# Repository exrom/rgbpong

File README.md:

# RGB modification for AY-3-8500 based game consoles

## Problems without an rgb output

The [AY-3-8500](https://en.wikipedia.org/wiki/AY-3-8500) is an integrated circuit from the 1970's used in pong-like video gaming consoles.
These consoles have an antenna output where the video signal is modulated onto a VHF channel.
The video quality is very poor because of the nature of a composite video and the VHF back and forth conversion.

Some consoles have a colored output where the playing field, the ball and the left and right paddle have different colors. This is possible because the AY-3-8500 provides separate signals for them.
A curcuit of logic gates generates different phased color carriers and combies each picture signal with one of them in order to get the colored output.
The color generation is very simple and the resulting composite video signal might not be completely compatible with the standards.
A wrong adjusted color carrier frequency might also lead to a TV not showing the colors at all and fall back to a b/w video.
 
Now there are modifications for having a composite video output for such consoles like 
[this one](https://circuit-board.de/forum/index.php/Thread/11658-Umbau-von-Universum-4106-Color-Video-Out/). 
Though this already provides better video quality as the HF conversion is skipped, the quality and stability of the video is still not perfect.

Composite video signals have - in contrast to rgb - a systematic problem: luminance and color signals disturb each other. Aka [dot crawl](https://en.wikipedia.org/wiki/Dot_crawl).

In my case, i got a UNIVERSUM Multi Color Spiel 4106 with PAL color output and wanted to connect it to a modern flat screen TV which did not show the colors correctly. You might also use this rgb mod to add colored output if your console is just black/white.

## The RGB modification

### AY-3 signals

The AY-3-8500 has this pinout:

.
 
It works with 6...7V. In my case a voltage regulator will limit battery voltage to 6.1V.

We need to connect to these pins:

| signal                         |  pin  |
|--------------------------------|-------|
| Vss (ground)                   |  2    |
| Sound output                   |  3    |
| Vcc (6.1V)                     |  4    |
| Ball output                    |  6    |
| Right player output            |  9    |
| Left player output             |  10   |
| Sync output                    |  16   |
| Score and Field output         |  24   |

All signals are active high (high voltage == bright).

### Color mapping

I decided to map the four signals to the red, green, blue inputs like this:

|          |   ball   | score & field  |  left    |  right   |
|----------|----------|----------------|----------|----------|
| 🔴 red      |    x     |      x         |    x     |          |
| 🟢 green    |    x     |      x         |          |    x     |
| 🔵 blue     |    x     |                |    x     |    x     |
|----------|----------|----------------|----------|----------|
| color    | ⚪ white   |    🟡 yellow     | 🟣 purple  | 😱 sky blue |

(there is no unicode char for sky blue - sorry)

### SCART signals

I decided to interface to a [SCART connector](https://en.wikipedia.org/wiki/SCART) which provides rgb input on a TV - at least in europe.

| signal                         |  pin  |  remark                       |
|--------------------------------|-------|-------------------------------|
| red video                      |  15   |  0.7 Vpp, 75 ohms             |
| green video                    |  11   |  0.7 Vpp, 75 ohms             |
| blue  video                    |  7    |  0.7 Vpp, 75 ohms             |
| RGB video selection            |  16   |  0..0.4V=composite, 1..3V=RGB |
| composite video                |  20   |  1 Vpp, 75 ohms               |
| audio input                    |  2+6  |  0.40 mVrms, > 47K ohms       |
| GND signals 14, 7,18,5,9,13    |       |                               |

### Circuit

The AY-3-8500 signals are TTL (more precisely the supply voltage of AY - may be 6..9V).
The 74HC4075 (3-input OR gates) does the color mapping and can work directly with the AY signals.
Output current of 74HC is too weak to drive a 75Ohms video out so we need to amplify.
A npn transistor is used as emitter follower to amplify the current (not the voltage).
After T1-T3, we have VCC-0,7V. Video out has 1V max.
After T4 we need 0...0.3V for sync levels. 

The audio signal is actually not needed when the console itself has a built-in speaker.
Anyway it is fun to hear how the picture processing delays audio on a modern flat TV. Note that lightguns work only on 50/60Hz crt TVs, not on modern ones.
The circuit provies a jumper for audio on/off.

The composite video is needed on the SCART connector for sync even if it may be present in the rgb signals. A TV takes extracts sync information from the composite video pin. If pin 16 is 1..3V the rgb input is selected and any picture information on pin 19 is ignored.
I originally tried to re-use the already present composite signal which is generated inside the game console. But this signal turned out to generate unstable picture on some TVs as it is very high resistive and grabbing it may influence internal signal leves too much.
Anyhow, if the sync info is taken directly from AY, we do not use any other signal from the console which means, one can actually build up the whole game system just with the AY and some paddles/switches.

When only signals from the AY are taken, one can make such a intermediate socket which can be inserted into the console without soldering.

And here is the schematic

The 1kOhms R7 pull up is needed because the consoles internal circuitry loads the AY's ball pin too much the resulting level the 74HC did not recognize as low.

For T1,T2,T3 almost any bipolar npn type should do the job.
Note: A BC547 has pin out C-B-E but on the board the C is in the middle. It just was easier to route. You need to cross the pins.

The schematic and the board are available for KiCAD 8.0 (thanks to just-some-tall-bloke) and EAGLE.

### Photos

Original console's video signal quality with just the composite mod (quality of the antenna signal is even worse). One can see the dot crawl and some background noise.

After the rgb mod

board

### Good luck

I like to know when you build this rgb mod, please drop me a mail. Also any other feedback is welcome.

Greetings go to my very good friend Sven.

Happy retro gaming! 

### other retro game projects

[Siemens BILDMEISTER Turnier FZ 2001 video modification](bildmeister.md)

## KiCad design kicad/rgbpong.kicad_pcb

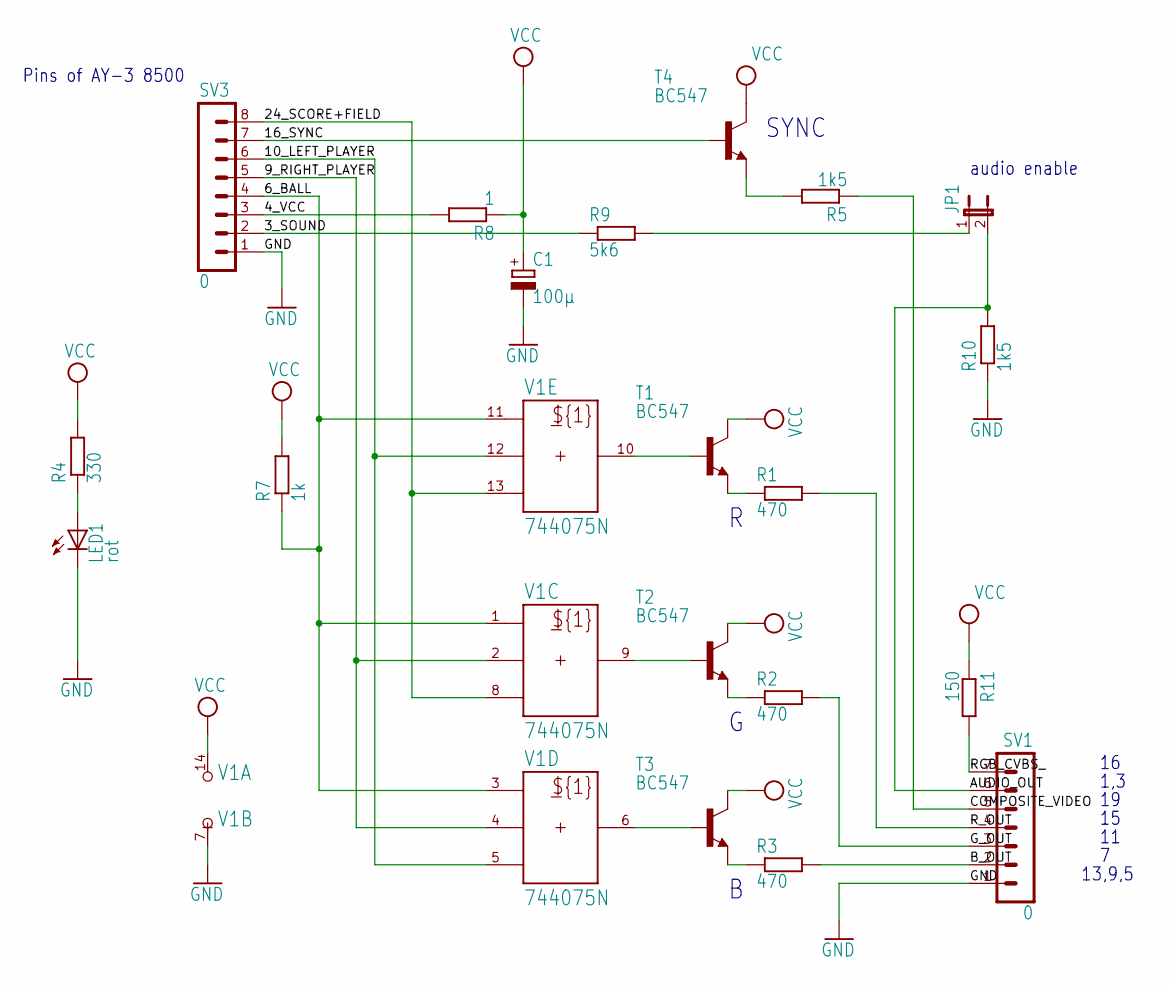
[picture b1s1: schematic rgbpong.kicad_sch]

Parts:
C1: 100µ; E2,5-5
JP1: 0; JP1
LED1: rot; LED3MM
R1, R2, R3: 470; 0207_10
R4: 330; 0207_10
R5, R10: 1k5; 0207_10
R7: 1k; 0207_15
R8: 1; 0207_15
R9: 5k6; 0207_10
R11: 150; 0207_10
SV1: 0; MA07-1
SV3: 0; MA08-1
T1, T2, T3, T4: BC547; TO92-ECB
V1: 744075N; DIL14

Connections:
3_SOUND: R9.1, SV3.2
4_VCC: R8.2, SV3.3
6_BALL: R7.1, SV3.4, V1.1 (A), V1.3 (A), V1.11 (A)
9_RIGHT_PLAYER: SV3.5, V1.2 (B), V1.4 (B)
10_LEFT_PLAYER: SV3.6, V1.5 (C), V1.12 (B)
16_SYNC: SV3.7, T4.B
24_SCORE+FIELD: SV3.8, V1.8 (C), V1.13 (C)
AUDIO_OUT: JP1.2, R10.2, SV1.6
B_OUT: R3.2, SV1.2
B_TTL: T3.B, V1.6 (Y)
COMPOSITE_VIDEO: R5.1, SV1.5
GND: C1.-, LED1.K (C), R10.1, SV1.1, SV3.1, V1.7 (-UB)
G_OUT: R2.2, SV1.3
G_TTL: T2.B, V1.9 (Y)
unnamed: LED1.A, R4.1
unnamed: R5.2, T4.E
unnamed: R1.1, T1.E
unnamed: R2.1, T2.E
unnamed: R3.1, T3.E
unnamed: JP1.1, R9.2
RGB_CVBS_: R11.2, SV1.7
R_OUT: R1.2, SV1.4
R_TTL: T1.B, V1.10 (Y)
VCC: C1.+, R4.2, R7.2, R8.1, R11.1, T1.C, T2.C, T3.C, T4.C, V1.14 (+UB)

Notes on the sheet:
SYNC
13,9,5
1,3
audio enable
Pins of AY-3 8500

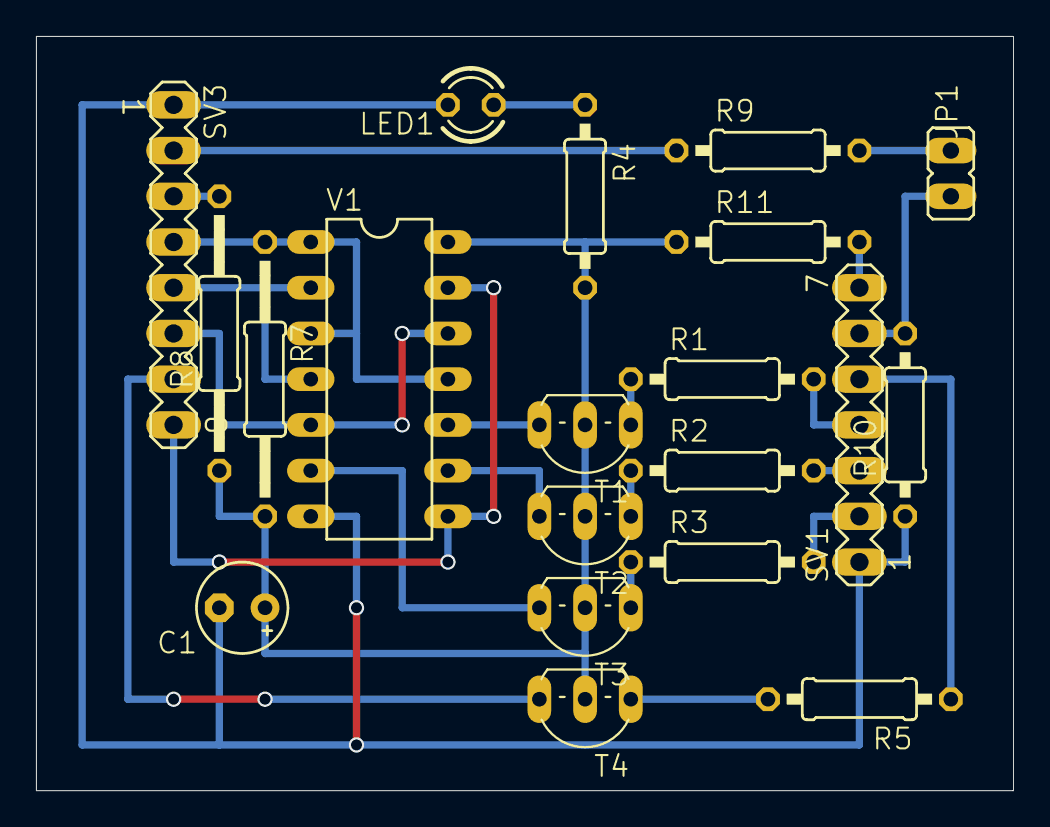
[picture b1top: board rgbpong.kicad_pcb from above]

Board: 2 copper layers, 54.3 x 41.9 mm, 20 parts (0 on the bottom side), 24 nets.

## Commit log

2019-05-09 1st version
2022-12-28 add Siemens BILDMEISTER Turnier FZ 2001 video modification
    + fix pinout of SCART connector
2022-12-28 add colored circles in mapping table
2025-10-12 update for KiCAD: README.md + ignored files
    rgbpong.kicad_pcb and rgbpong.kicad_sch open successfully with KiCAD V9.0.5
